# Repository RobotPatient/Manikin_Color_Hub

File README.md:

# Manikin_Color_Hub

Welcome to the Manikin Color Hub, a part of the skin color research team RGBbaby. 
Here's an overview of our file structure:

# Manikin Colour Hub

## Led Driver Board Files, Flexible LED Strip PCBs, and Software

Welcome to the Manikin Colour Hub, a part of the skin colour research group RGBbaby. Here's an overview of our file structure:

### Arduino Spectrometer:

Contains CAD and code files for the AS7341 colour sensor. Use this sensor setup to analyze the light emitted by a specific sample.

### General Docs:

- **Product_report - individual reports:** Individual project files included in the product report.
- **Product Report:** Detailed report on our project.
- **Progress Report:** Overview of our progress.
- **Initial Questions and Answers from WKZ:** Compilation of our initial queries and responses.
- **Manual:** Comprehensive guide for our project.
- **ToDo List:** List of tasks yet to be completed.

### Led Test Setup:

Code for testing a bare neopixel LED strip in combination with an Adafruit Feather M0 Express.

### PCBs:

- **LedDriverBoardV1:** KiCad files and schematic for the first version of our LED driver board.
- **LedDriverBoardV2:** KiCad files, schematic, code, and flexible PCBs for the second version of our LED driver board.
- **LedDriverBoardV3:** KiCad files, schematic, code, and flexible PCBs for the third and final version of our LED driver board.

### Pi Spectrometer:

CAD files for the Raspberry Pi-based spectrometer.

Feel free to explore and contribute to the Manikin Color Hub's diverse set of files and resources. 
If you have questions, reach out to us!

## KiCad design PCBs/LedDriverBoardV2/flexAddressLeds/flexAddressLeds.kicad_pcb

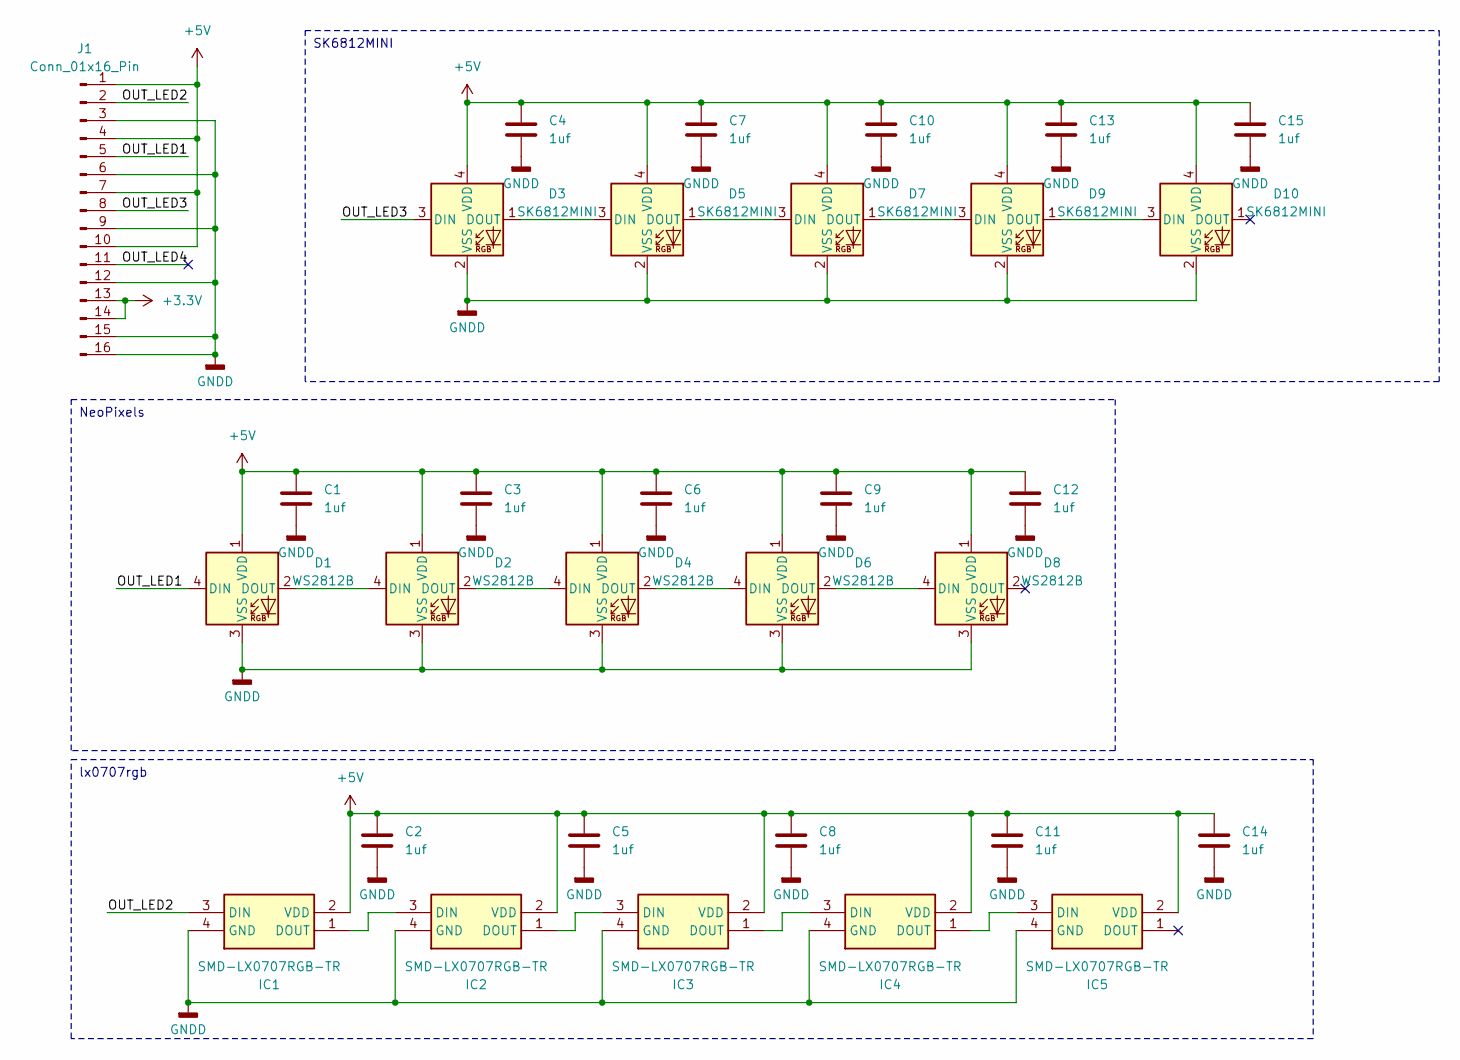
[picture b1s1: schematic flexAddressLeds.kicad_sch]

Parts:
C1, C2, C3, C4, C5, C6, C7, C8, C9, C10, C11, C12, C13, C14, C15: 1uf; C_0603_1608Metric_Pad1.08x0.95mm_HandSolder
D1, D2, D4, D6, D8: WS2812B; LED_WS2812B_PLCC4_5.0x5.0mm_P3.2mm
D3, D5, D7, D9, D10: SK6812MINI; LED_SK6812MINI_PLCC4_3.5x3.5mm_P1.75mm
IC1, IC2, IC3, IC4, IC5: SMD-LX0707RGB-TR; SMDLX0707RGBTR; Manufacturer_Part_Number SMD-LX0707RGB-TR; Mouser Part Number 696-SMDLX0707RGBTR
J1: Conn_01x16_Pin; Conn_1x16_FFC

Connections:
+3.3V: J1.13, J1.14
+5V: C1.1, C2.1, C3.1, C4.1, C5.1, C6.1, C7.1, C8.1, C9.1, C10.1, C11.1, C12.1, C13.1, C14.1, C15.1, D1.1 (VDD), D2.1 (VDD), D3.4 (VDD), D4.1 (VDD), D5.4 (VDD), D6.1 (VDD), D7.4 (VDD), D8.1 (VDD), D9.4 (VDD), D10.4 (VDD), IC1.2 (VDD), IC2.2 (VDD), IC3.2 (VDD), IC4.2 (VDD), IC5.2 (VDD), J1.1, J1.4, J1.7, J1.10
/OUT_LED1: D1.4 (DIN), J1.5
/OUT_LED2: IC1.3 (DIN), J1.2
/OUT_LED3: D3.3 (DIN), J1.8
/OUT_LED4: J1.11
GNDD: C1.2, C2.2, C3.2, C4.2, C5.2, C6.2, C7.2, C8.2, C9.2, C10.2, C11.2, C12.2, C13.2, C14.2, C15.2, D1.3 (VSS), D2.3 (VSS), D3.2 (VSS), D4.3 (VSS), D5.2 (VSS), D6.3 (VSS), D7.2 (VSS), D8.3 (VSS), D9.2 (VSS), D10.2 (VSS), IC1.4 (GND), IC2.4 (GND), IC3.4 (GND), IC4.4 (GND), IC5.4 (GND), J1.3, J1.6, J1.9, J1.12, J1.15, J1.16
unnamed: D1.2 (DOUT), D2.4 (DIN)
unnamed: D2.2 (DOUT), D4.4 (DIN)
unnamed: D3.1 (DOUT), D5.3 (DIN)
unnamed: D4.2 (DOUT), D6.4 (DIN)
unnamed: D5.1 (DOUT), D7.3 (DIN)
unnamed: D6.2 (DOUT), D8.4 (DIN)
unnamed: D7.1 (DOUT), D9.3 (DIN)
unnamed: D9.1 (DOUT), D10.3 (DIN)
unnamed: IC1.1 (DOUT), IC2.3 (DIN)
unnamed: IC2.1 (DOUT), IC3.3 (DIN)
unnamed: IC3.1 (DOUT), IC4.3 (DIN)
unnamed: IC4.1 (DOUT), IC5.3 (DIN)

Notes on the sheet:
lx0707rgb
NeoPixels
SK6812MINI

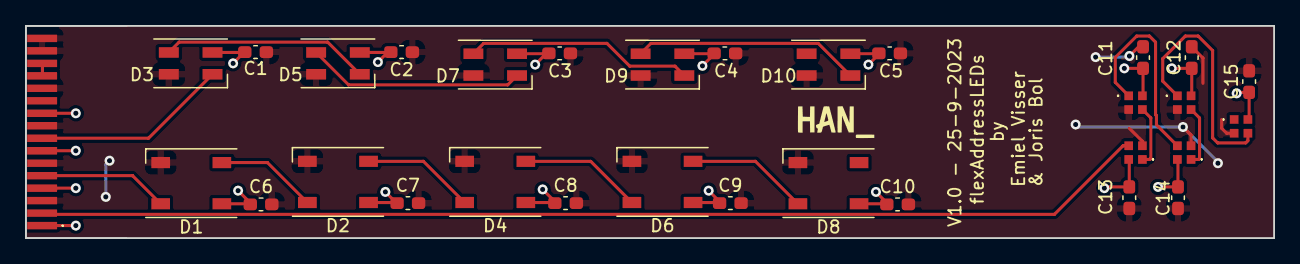
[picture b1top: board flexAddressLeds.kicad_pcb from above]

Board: 2 copper layers, 100.0 x 17.0 mm, 31 parts (0 on the bottom side), 18 nets.

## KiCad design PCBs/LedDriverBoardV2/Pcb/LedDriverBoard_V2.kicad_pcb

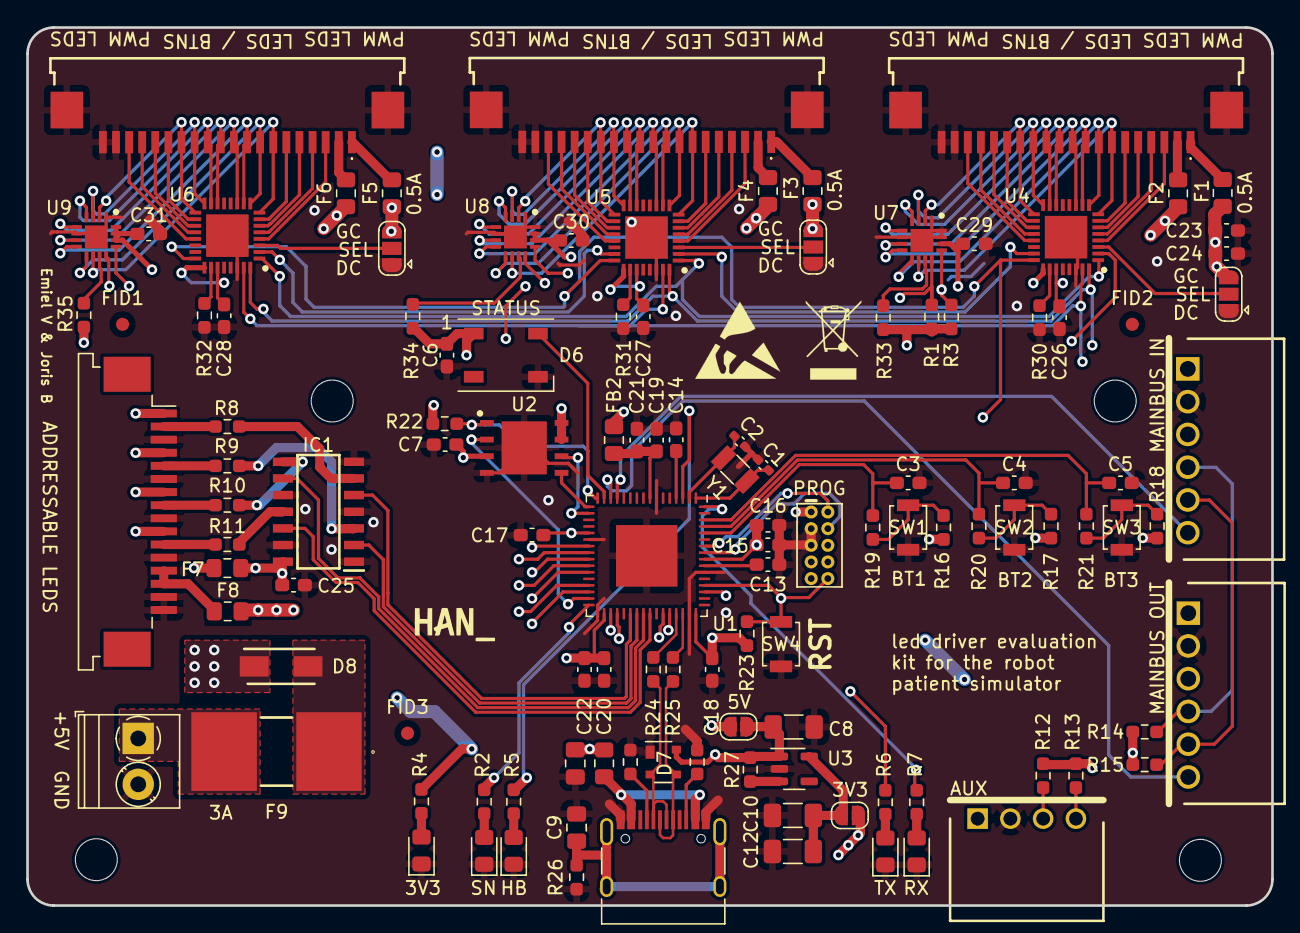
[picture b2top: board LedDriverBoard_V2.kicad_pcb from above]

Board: 4 copper layers, 95.0 x 67.0 mm, 122 parts (0 on the bottom side), 136 nets.

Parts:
C1, C2: 2pF; C_0402_1005Metric_Pad0.74x0.62mm_HandSolder
C3, C4, C5, C13, C16, C21, C22: 10uF; C_0603_1608Metric_Pad1.08x0.95mm_HandSolder
C6, C14: 1uF; C_0603_1608Metric_Pad1.08x0.95mm_HandSolder
C7, C15, C17, C18, C19, C20, C23, C25, C26, C27, C28, C29, C30, C31: 100nF; C_0603_1608Metric_Pad1.08x0.95mm_HandSolder
C8, C10: 10uF; C_1206_3216Metric_Pad1.33x1.80mm_HandSolder
C9: 4.7nF 1kV; C_0805_2012Metric_Pad1.18x1.45mm_HandSolder
C11: 100uF; C_0805_2012Metric_Pad1.18x1.45mm_HandSolder
C12: 1uF; C_1206_3216Metric_Pad1.33x1.80mm_HandSolder
C24: 4.7uF; C_0603_1608Metric_Pad1.08x0.95mm_HandSolder
D1: BLUE; LED_0805_2012Metric_Pad1.15x1.40mm_HandSolder
D2, D4: GREEN; LED_0805_2012Metric_Pad1.15x1.40mm_HandSolder
D3: RED; LED_0805_2012Metric_Pad1.15x1.40mm_HandSolder
D5: ORANGE; LED_0805_2012Metric_Pad1.15x1.40mm_HandSolder
D6: WS2812B; LED_WS2812B_PLCC4_5.0x5.0mm_P3.2mm
D7: PRTR5V0U2X; SOT-143
D8: D_Schottky; DIOM5127X229N
F1, F2, F3, F4, F5, F6, F7, F8: Polyfuse; Fuse_0805_2012Metric_Pad1.15x1.40mm_HandSolder
F9: Fuse; 0031.7701.11
FB1, FB2: FerriteBead; L_0805_2012Metric_Pad1.15x1.40mm_HandSolder
FID1, FID2, FID3: Fiducial; Fiducial_1mm_Mask2mm
H1, H2, H3, H4: MountingHole; MountingHole_3.2mm_M3_DIN965
IC1: SN74AHCT125DR; SOIC127P600X175-14N
J1, J2, J3: FFC3B11-20-T; FFC3B1120T
J4: 1778641; SHDRRA4W60P0X250_1X4_1170X750X510P
J5: Conn_01x16_Pin; TE_1-84952-6_1x16-1MP_P1.0mm_Horizontal
J6, J7: 1778667; SHDRRA6W70P0X250_1X6_1670X750X510P
J8: CORTEX_DEBUGPTH; 2X5-PTH-1.27MM
J9: USB_C_Receptacle_USB2.0; USB_C_Receptacle_HRO_TYPE-C-31-M-12
J10: Conn_01x02_Socket; TerminalBlock_Phoenix_PT-1,5-2-3.5-H_1x02_P3.50mm_Horizontal
JP1, JP2: Jumper_2_Open; SolderJumper-2_P1.3mm_Open_RoundedPad1.0x1.5mm
JP3, JP4, JP5: Jumper_3_Open; SolderJumper-3_P1.3mm_Open_RoundedPad1.0x1.5mm
R1, R3, R12, R13, R14, R15: 4.7k; R_0603_1608Metric_Pad0.98x0.95mm_HandSolder
R2, R5, R7: 330; R_0603_1608Metric_Pad0.98x0.95mm_HandSolder
R4, R6: 470; R_0603_1608Metric_Pad0.98x0.95mm_HandSolder
R8, R9, R10, R11: 62; R_0603_1608Metric_Pad0.98x0.95mm_HandSolder
R16, R17, R18, R19, R20, R21, R22, R23, R33, R34, R35: 10k; R_0603_1608Metric_Pad0.98x0.95mm_HandSolder
R24, R25: 27; R_0603_1608Metric_Pad0.98x0.95mm_HandSolder
R26: 1m; R_0603_1608Metric_Pad0.98x0.95mm_HandSolder
R27: 100k; R_0603_1608Metric_Pad0.98x0.95mm_HandSolder
R28, R29: 5.1k 1%; R_0603_1608Metric_Pad0.98x0.95mm_HandSolder
R30, R31, R32: 2k; R_0603_1608Metric_Pad0.98x0.95mm_HandSolder
SW1, SW2, SW3, SW4: SW_Push; SW_SPST_B3U-1000P
U1: ATSAMD21J18A-M; QFN-64-1EP_9x9mm_P0.5mm_EP4.7x4.7mm
U2: IS25LP032D-JLLE; SON127P600X500X75-9N-D
U3: AP2112K-3.3; SOT-23-5
U4, U5, U6: TLC59401RHBR; QFN50P500X500X100-33N-D
U7, U8, U9: PCA9670BS,118; QFN50P300X300X100-17N-D
Y1: 32.768mHz; Crystal_SMD_3215-2Pin_3.2x1.5mm

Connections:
+3V3: C6.2, C7.2, C15.1, C16.1, C17.1, C18.1, C20.1, C22.1, C29.1, C30.1, C31.1, D6.1 (VDD), F2.1, F4.1, F6.1, F8.2, FB2.1, J4.1, J6.3, J7.3, J8.1 (VCC), JP2.2 (B), R1.1, R3.2, R4.1, R12.1, R13.2, R14.1, R15.2, R16.1, R17.1, R18.1, R22.1, R23.2, R33.2, R34.2, R35.2, U1.21 (VDDIO), U1.34 (VDDIO), U1.48 (VDDIO), U1.56 (VDDIN), U2.3 (~WP(IO2)), U2.7 (~HOLD(IO3)), U2.8 (VCC), U7.14 (VDD), U8.14 (VDD), U8.15 (AD0), U9.14 (VDD), U9.15 (AD0), U9.16 (AD1)
+5V: C23.1, C24.1, C25.1, C26.1, C27.1, C28.1, D8.1 (K), F1.1, F3.1, F5.1, F7.2, IC1.14 (VCC), J6.1, J7.1, JP1.2 (B), JP3.3 (B), JP4.3 (B), JP5.3 (B), U4.25 (TEST), U4.27 (VCC), U5.25 (TEST), U5.27 (VCC), U6.25 (TEST), U6.27 (VCC)
/ADR_LED1: IC1.2 (1A), U1.39 (PB16)
/ADR_LED2: IC1.5 (2A), U1.38 (PA19)
/ADR_LED3: IC1.9 (3A), U1.40 (PB17)
/ADR_LED4: IC1.12 (4A), U1.41 (PA20)
/AREF: C14.1, U1.4 (PA03)
/BTN1: C3.1, R19.2, U1.60 (PB31)
/BTN2: C4.1, R20.2, U1.61 (PB00)
/BTN3: C5.1, R21.2, U1.62 (PB01)
/D2_FLASHMISO: U1.31 (PA14), U2.2 (SO(IO1))
/D3_FLASHSCK: U1.18 (PA09), U2.6 (SCK)
/D4_FLASHMOSI: U1.17 (PA08), U2.5 (SI(IO0))
/D5_HEALTH: R2.1, U1.32 (PA15)
/D8_NEOPIXEL: D6.4 (DIN), U1.15 (PA06)
/D14_HB: R5.1, U1.3 (PA02)
/INT4: J6.6, U1.13 (PA04)
/INT5: J7.6, U1.14 (PA05)
/LED1-0: J1.3, U4.4 (OUT0)
/LED1-1: J1.4, U4.5 (OUT1)
/LED1-2: J1.5, U4.6 (OUT2)
/LED1-3: J1.6, U4.7 (OUT3)
/LED1-4: J1.7, U4.8 (OUT4), U7.10 (P7)
/LED1-5: J1.8, U4.9 (OUT5), U7.9 (P6)
/LED1-6: J1.9, U4.10 (OUT6), U7.8 (P5)
/LED1-7: J1.10, U4.11 (OUT7), U7.7 (P4)
/LED1-8: J1.11, U4.14 (OUT8), U7.5 (P3)
/LED1-9: J1.12, U4.15 (OUT9), U7.4 (P2)
/LED1-10: J1.13, U4.16 (OUT10), U7.3 (P1)
/LED1-11: J1.14, U4.17 (OUT11), U7.2 (P0)
/LED1-12: J1.15, U4.18 (OUT12)
/LED1-13: J1.16, U4.19 (OUT13)
/LED1-14: J1.17, U4.20 (OUT14)
/LED1-15: J1.18, U4.21 (OUT15)
/LED2-0: J2.3, U5.4 (OUT0)
/LED2-1: J2.4, U5.5 (OUT1)
/LED2-2: J2.5, U5.6 (OUT2)
/LED2-3: J2.6, U5.7 (OUT3)
/LED2-4: J2.7, U5.8 (OUT4), U8.10 (P7)
/LED2-5: J2.8, U5.9 (OUT5), U8.9 (P6)
/LED2-6: J2.9, U5.10 (OUT6), U8.8 (P5)
/LED2-7: J2.10, U5.11 (OUT7), U8.7 (P4)
/LED2-8: J2.11, U5.14 (OUT8), U8.5 (P3)
/LED2-9: J2.12, U5.15 (OUT9), U8.4 (P2)
/LED2-10: J2.13, U5.16 (OUT10), U8.3 (P1)
/LED2-11: J2.14, U5.17 (OUT11), U8.2 (P0)
/LED2-12: J2.15, U5.18 (OUT12)
/LED2-13: J2.16, U5.19 (OUT13)
/LED2-14: J2.17, U5.20 (OUT14)
/LED2-15: J2.18, U5.21 (OUT15)
/LED3-0: J3.3, U6.4 (OUT0)
/LED3-1: J3.4, U6.5 (OUT1)
/LED3-2: J3.5, U6.6 (OUT2)
/LED3-3: J3.6, U6.7 (OUT3)
/LED3-4: J3.7, U6.8 (OUT4), U9.10 (P7)
/LED3-5: J3.8, U6.9 (OUT5), U9.9 (P6)
/LED3-6: J3.9, U6.10 (OUT6), U9.8 (P5)
/LED3-7: J3.10, U6.11 (OUT7), U9.7 (P4)
/LED3-8: J3.11, U6.14 (OUT8), U9.5 (P3)
/LED3-9: J3.12, U6.15 (OUT9), U9.4 (P2)
/LED3-10: J3.13, U6.16 (OUT10), U9.3 (P1)
/LED3-11: J3.14, U6.17 (OUT11), U9.2 (P0)
/LED3-12: J3.15, U6.18 (OUT12)
/LED3-13: J3.16, U6.19 (OUT13)
/LED3-14: J3.17, U6.20 (OUT14)
/LED3-15: J3.18, U6.21 (OUT15)
/LEDBLANK: U1.27 (PB14), U4.31 (BLANK), U5.31 (BLANK), U6.31 (BLANK)
/LEDGSLCK: U1.26 (PB13), U4.24 (GSCLK), U5.24 (GSCLK), U6.24 (GSCLK)
/LEDSCLK: U1.24 (PB11), U4.1 (SCLK), U5.1 (SCLK), U6.1 (SCLK)
/LEDSIN: U1.23 (PB10), U4.2 (SIN)
/LEDXLAT: U1.25 (PB12), U4.32 (XLAT), U5.32 (XLAT), U6.32 (XLAT)
/LedDriver/LEDMODE1: JP3.2 (C), U4.3 (MODE)
/LedDriver/LEDMODE2: JP5.2 (C), U5.3 (MODE)
/LedDriver/LEDMODE3: JP4.2 (C), U6.3 (MODE)
/LedDriver/LEDSOUT-1: U4.23 (SOUT), U5.2 (SIN)
/LedDriver/LEDSOUT-2: U5.23 (SOUT), U6.2 (SIN)
/OUT_LED1: IC1.3 (1Y), R9.1
/OUT_LED2: IC1.6 (2Y), R8.1
/OUT_LED3: IC1.8 (3Y), R10.1
/OUT_LED4: IC1.11 (4Y), R11.1
/PA0_XTAL: C1.2, U1.1 (PA00), Y1.2
/PA1_XTAL: C2.2, U1.2 (PA01), Y1.1
/PA7_FLASH_CS: R22.2, U1.16 (PA07), U2.1 (~CE)
/Power/3.3v: C10.1, C12.1, JP2.1 (A), U3.5 (VOUT)
/Power/SHIELD: C9.1, J9.S1 (SHIELD), R26.1
/RXLED: R7.1, U1.64 (PB03)
/SCL: J6.4, J7.4, R14.2, U1.44 (PA23)
/SCL_IO: R1.2, U1.36 (PA17), U7.12 (SCL), U8.12 (SCL), U9.12 (SCL)
/SCL_SENSOR_D13: J4.3, R12.2, U1.30 (PA13)
/SDA: J6.5, J7.5, R15.1, U1.43 (PA22)
/SDA_IO: R3.1, U1.35 (PA16), U7.13 (SDA), U8.13 (SDA), U9.13 (SDA)
/SDA_SENSOR_D11: J4.4, R13.1, U1.29 (PA12)
/SWCLK: J8.4 (SWDCLK/TCK), U1.57 (PA30)
/SWDIO: J8.2 (SWDIO/TMS), U1.58 (PA31)
/TXLED: R6.1, U1.51 (PA27)
/USB_D+: D7.3 (I/O2), J9.A6 (D+), J9.B6 (D+), R25.1
/USB_D-: D7.2 (I/O1), J9.A7 (D-), J9.B7 (D-), R24.1
/USB_TERM_D+: R25.2, U1.46 (PA25)
/USB_TERM_D-: R24.2, U1.45 (PA24)
/VDDANA: C19.1, C21.1, FB2.2, U1.8 (VDDANA)
/VDDCORE: C13.2, U1.55 (VDDCORE)
/~RESET: J8.10 (NRESET), R23.1, SW4.1, U1.52 (~RESET)
GNDD: C1.1, C2.1, C3.2, C4.2, C5.2, C6.1, C7.1, C8.2, C9.2, C10.2, C11.2, C12.2, C13.1, C14.2, C15.2, C16.2, C17.2, C18.2, C19.2, C20.2, C21.2, C22.2, C23.2, C24.2, C25.2, C26.2, C27.2, C28.2, C29.2, C30.2, C31.2, D1.1 (K), D2.1 (K), D3.1 (K), D4.1 (K), D5.1 (K), D6.3 (VSS), D7.1 (GND), IC1.1 (1~OE), IC1.4 (2~OE), IC1.7 (GND), IC1.10 (3~OE), IC1.13 (4~OE), J1.19, J1.20, J1.MP1, J1.MP2, J2.19, J2.20, J2.MP1, J2.MP2, J3.19, J3.20, J3.MP1, J3.MP2, J4.2, J5.3, J5.6, J5.9, J5.12, J5.15, J5.16, J6.2, J7.2, J8.3 (GND), J8.5 (GND), J9.A1 (GND), J9.A12 (GND), J9.B1 (GND), J9.B12 (GND), J10.2, JP3.1 (A), JP4.1 (A), JP5.1 (A), R26.2, R28.2, R29.2, R30.2, R31.2, R32.2, SW1.1, SW2.1, SW3.1, SW4.2, U1.7 (GNDANA), U1.22 (GND), U1.33 (GND), U1.47 (GND), U1.54 (GND), U1.65 (EP), U2.4 (GND), U2.9 (EP), U3.2 (GND), U4.30 (GND), U4.33 (EP), U5.30 (GND), U5.33 (EP), U6.30 (GND), U6.33 (EP), U7.1 (AD2), U7.6 (VSS), U7.15 (AD0), U7.16 (AD1), U7.17 (EP), U8.1 (AD2), U8.6 (VSS), U8.16 (AD1), U8.17 (EP), U9.1 (AD2), U9.6 (VSS), U9.17 (EP)
unnamed: D1.2 (A), R2.2
unnamed: D2.2 (A), R4.2
unnamed: D3.2 (A), R5.2
unnamed: D4.2 (A), R6.2
unnamed: D5.2 (A), R7.2
unnamed: D8.2 (A), F9.1
unnamed: F1.2, J1.1
unnamed: F2.2, J1.2
unnamed: F3.2, J2.1
unnamed: F4.2, J2.2
unnamed: F5.2, J3.1
unnamed: F6.2, J3.2
unnamed: FB1.1, J9.A4 (VBUS), J9.A9 (VBUS), J9.B4 (VBUS), J9.B9 (VBUS)
unnamed: F7.1, J5.1, J5.4, J5.7, J5.10
unnamed: J5.2, R8.2
unnamed: J5.5, R9.2
unnamed: J5.8, R10.2
unnamed: J5.11, R11.2
unnamed: F8.1, J5.13, J5.14
unnamed: J9.A5 (CC1), R29.1
unnamed: J9.B5 (CC2), R28.1
unnamed: F9.2, J10.1
unnamed: R16.2, R19.1, SW1.2
unnamed: R17.2, R20.1, SW2.2
unnamed: R18.2, R21.1, SW3.2
unnamed: R27.2, U3.3 (EN)
unnamed: R30.1, U4.26 (IREF)
unnamed: R31.1, U5.26 (IREF)
unnamed: R32.1, U6.26 (IREF)
unnamed: R33.1, U7.11 (~RESET)
unnamed: R34.1, U8.11 (~RESET)
unnamed: R35.1, U9.11 (~RESET)
VBUS: C8.1, C11.1, D7.4 (VCC), FB1.2, JP1.1 (A), R27.1, U3.1 (VIN)

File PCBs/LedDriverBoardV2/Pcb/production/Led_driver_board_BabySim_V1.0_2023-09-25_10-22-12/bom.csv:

Designator,Footprint,Quantity,Value,LCSC Part #
"C1, C2",0402,2,2pF,
"C10, C8",1206,2,10uF,
C11,0805,1,100uF,
C12,1206,1,1uF,
"C13, C16, C21, C22, C3, C4, C5",0603,7,10uF,
"C14, C6",0603,2,1uF,
"C15, C17, C18, C19, C20, C23, C25, C26, C27, C28, C29, C30, C31, C7",0603,14,100nF,
C24,0603,1,4.7uF,
C9,0805,1,4.7nF 1kV,
D1,0805,1,BLUE,
"D2, D4",0805,2,GREEN,
D3,0805,1,RED,
D5,0805,1,ORANGE,
D6,LED_WS2812B_PLCC4_5.0x5.0mm_P3.2mm,1,WS2812B,
D7,SOT-143,1,PRTR5V0U2X,
D8,DIOM5127X229N,1,D_Schottky,
"F1, F2, F3, F4, F5, F6, F7, F8",0805,8,Polyfuse,
F9,0031.7701.11,1,Fuse,
"FB1, FB2",0805,2,FerriteBead,
"FID1, FID2, FID3",Fiducial_1mm_Mask2mm,3,Fiducial,
"H1, H2, H3, H4",MountingHole_3.2mm_M3_DIN965,4,MountingHole,
IC1,SOIC127P600X175-14N,1,SN74AHCT125DR,
"J1, J2, J3",FFC3B1120T,3,FFC3B11-20-T,
J10,"TerminalBlock_Phoenix_PT-1,5-2-3.5-H_1x02_P3.50mm_Horizontal",1,Conn_01x02_Socket,
J4,SHDRRA4W60P0X250_1X4_1170X750X510P,1,1778641,
J5,TE_1-84952-6_1x16-1MP_P1.0mm_Horizontal,1,Conn_01x16_Pin,
"J6, J7",SHDRRA6W70P0X250_1X6_1670X750X510P,2,1778667,
J8,2X5-PTH-1.27MM,1,CORTEX_DEBUGPTH,
J9,USB_C_Receptacle_HRO_TYPE-C-31-M-12,1,USB_C_Receptacle_USB2.0,
"JP1, JP2",SolderJumper-2_P1.3mm_Open_RoundedPad1.0x1.5mm,2,Jumper_2_Open,
"JP3, JP4, JP5",SolderJumper-3_P1.3mm_Open_RoundedPad1.0x1.5mm,3,Jumper_3_Open,
"R1, R12, R13, R14, R15, R3",0603,6,4.7k,
"R10, R11, R8, R9",0603,4,62,
"R16, R17, R18, R19, R20, R21, R22, R23, R33, R34, R35",0603,11,10k,
"R2, R5, R7",0603,3,330,
"R24, R25",0603,2,27,
R26,0603,1,1m,
R27,0603,1,100k,
"R28, R29",0603,2,5.1k 1%,
"R30, R31, R32",0603,3,2k,
"R4, R6",0603,2,470,
"SW1, SW2, SW3, SW4",SW_SPST_B3U-1000P,4,SW_Push,
U1,QFN-64-1EP_9x9mm_P0.5mm_EP4.7x4.7mm,1,ATSAMD21J18A-M,
U2,SON127P600X500X75-9N-D,1,IS25LP032D-JLLE,
U3,SOT-23-5,1,AP2112K-3.3,
"U4, U5, U6",QFN50P500X500X100-33N-D,3,TLC59401RHBR,
"U7, U8, U9",QFN50P300X300X100-17N-D,3,"PCA9670BS,118",
Y1,Crystal_SMD_3215-2Pin_3.2x1.5mm,1,32.768mHz,

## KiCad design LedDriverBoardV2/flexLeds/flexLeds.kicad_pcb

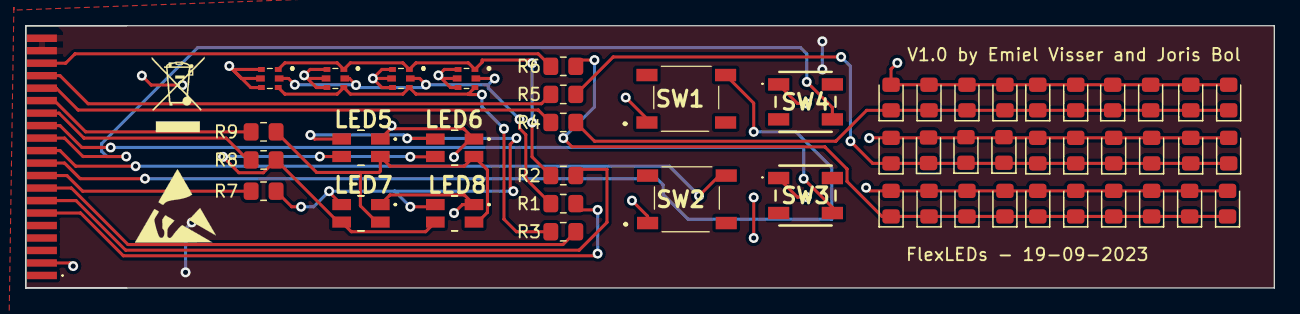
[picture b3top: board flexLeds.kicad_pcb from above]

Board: 2 copper layers, 100.0 x 21.0 mm, 52 parts (0 on the bottom side), 24 nets.

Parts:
D1, D2, D3, D4, D5, D6, D7, D8, D9, D10: RED; LED_0805_2012Metric_Pad1.15x1.40mm_HandSolder
D11, D12, D13, D14, D15, D16, D17, D18, D19, D20: GREEN; LED_0805_2012Metric_Pad1.15x1.40mm_HandSolder
D21, D22, D23, D24, D25, D26, D27, D28, D29, D30: BLUE; LED_0805_2012Metric_Pad1.15x1.40mm_HandSolder
J1: Conn_01x20_Pin; Conn_1x20_FFC
LED1, LED2, LED3, LED4: 19-337C_RSBHGHC-A01_2T; 19337CRSBHGHCA012T
LED5, LED6, LED7, LED8: 150141M173100
R1, R2, R3, R4, R5, R6, R7, R8, R9: R; R_0805_2012Metric_Pad1.20x1.40mm_HandSolder
SW1, SW2: SW_Push_Dual; TL3342F260QG
SW3, SW4: SW_Push_Dual; TS174805YE160SMTTR

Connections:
+3V3: D1.2 (A), D2.2 (A), D3.2 (A), D4.2 (A), D5.2 (A), D6.2 (A), D7.2 (A), D8.2 (A), D9.2 (A), D10.2 (A), D11.2 (A), D12.2 (A), D13.2 (A), D14.2 (A), D15.2 (A), D16.2 (A), D17.2 (A), D18.2 (A), D19.2 (A), D20.2 (A), D21.2 (A), D22.2 (A), D23.2 (A), D24.2 (A), D25.2 (A), D26.2 (A), D27.2 (A), D28.2 (A), D29.2 (A), D30.2 (A), J1.2, LED1.2 (A_GREEN), LED1.4 (A_RED), LED1.6 (A_BLUE), LED2.2 (A_GREEN), LED2.4 (A_RED), LED2.6 (A_BLUE), LED3.2 (A_GREEN), LED3.4 (A_RED), LED3.6 (A_BLUE), LED4.2 (A_GREEN), LED4.4 (A_RED), LED4.6 (A_BLUE), LED5.1 (COM_A), LED6.1 (COM_A), LED7.1 (COM_A), LED8.1 (COM_A), SW1.1, SW2.1, SW3.1, SW4.1
/LED-3: J1.6, R1.1
/LED-4: J1.7, R2.1
/LED-5: J1.8, R3.1
/LED-6: J1.9, R7.1
/LED-7: J1.10, SW1.4
/LED-8: J1.11, SW2.4
/LED-9: J1.12, SW4.4
/LED-10: J1.13, SW3.4
/LED-11: J1.14, R8.1
/LED-12: J1.15, R9.1
/LED-13: J1.16, R4.2
/LED-14: J1.17, R5.2
/LED-15: J1.18, R6.2
GNDD: J1.19, J1.20
unnamed: D1.1 (K), D2.1 (K), D3.1 (K), D4.1 (K), D5.1 (K), D6.1 (K), D7.1 (K), D8.1 (K), D9.1 (K), D10.1 (K), R4.1
unnamed: D11.1 (K), D12.1 (K), D13.1 (K), D14.1 (K), D15.1 (K), D16.1 (K), D17.1 (K), D18.1 (K), D19.1 (K), D20.1 (K), R5.1
unnamed: D21.1 (K), D22.1 (K), D23.1 (K), D24.1 (K), D25.1 (K), D26.1 (K), D27.1 (K), D28.1 (K), D29.1 (K), D30.1 (K), R6.1
unnamed: LED1.5 (K_BLUE), LED2.5 (K_BLUE), LED3.5 (K_BLUE), LED4.5 (K_BLUE), R3.2
unnamed: LED1.1 (K_GREEN), LED2.1 (K_GREEN), LED3.1 (K_GREEN), LED4.1 (K_GREEN), R2.2
unnamed: LED1.3 (K_RED), LED2.3 (K_RED), LED3.3 (K_RED), LED4.3 (K_RED), R1.2
unnamed: LED5.2 (K_B), LED6.2 (K_B), LED7.2 (K_B), LED8.2 (K_B), R9.2
unnamed: LED5.4 (K_G), LED6.4 (K_G), LED7.4 (K_G), LED8.4 (K_G), R8.2
unnamed: LED5.3 (K_R), LED6.3 (K_R), LED7.3 (K_R), LED8.3 (K_R), R7.2

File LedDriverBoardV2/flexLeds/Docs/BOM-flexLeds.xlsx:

Catagory | Name in schematic: | Name/Value | Mounting type | Footprint: | Nr. per. PCB: | Amount of PCBs: | Total amount: | To order: | Price per.part: | Price total: | Link:
LED | D6,D4,D5,D3,D9,D7,D1,D8,D10,D2 | RED | SMD | 0805 | 10 | 2 | 20 | 30 | 0.251 | 7.53 | https://nl.mouser.com/ProductDetail/Lite-On/LTST-C171KRKT?qs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
LED | D11,D19,D18,D14,D16,D13,D17,D15,D20,D12 | GREEN | SMD | 0805 | 10 | 2 | 20 | 30 | 0.214 | 6.42 | https://nl.mouser.com/ProductDetail/Lite-On/LTST-C171GKT?qs=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
LED | D30,D24,D21,D28,D22,D26,D27,D25,D29,D23 | BLUE | SMD | 0805 | 10 | 2 | 20 | 30 | 0.28799999999999998 | 8.6399999999999988 | https://nl.mouser.com/ProductDetail/Lite-On/LTST-C171TBKT?qs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
LED | LED8,LED7,LED5,LED6 | 150141M173100 | SMD | 150141M173100 | 4 | 2 | 8 | 10 | 0.46 | 4.6000000000000005 | https://nl.mouser.com/ProductDetail/Wurth-Elektronik/150141M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
LED | LED3,LED4,LED2,LED1 | 19337CRSBHGHCA012T | SMD | 19337CRSBHGHCA012T | 4 | 2 | 8 | 10 | 0.3 | 3 | https://www.digikey.nl/en/products/detail/everlight-electron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
SWITCH | SW2,SW1 | TL3342F260QG | SMD | TL3342F260QG | 2 | 2 | 4 | 5 | 0.61 | 3.05 | https://nl.mouser.com/ProductDetail/E-Switch/TL3342F260QG?qs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
SWITCH | SW3,SW4 | TS174805YE160SMTTR | SMD | TS174805YE160SMTTR | 2 | 2 | 4 | 5 | 0.26 | 1.3 | https://nl.mouser.com/ProductDetail/CUI-Devices/TS17-48-05-Y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
RESISTOR | R4, R5, R6 | 20ohm | SMD | 0805 | 3 | 2 | 6 | 10 | 4.7E-2 | 0.47 | https://nl.mouser.com/ProductDetail/Panasonic/ERJ-P06J200V?q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
RESISTOR | R1, R2, R3, R7, R8, R9 | 165ohm | SMD | 0805 | 6 | 2 | 12 | 20 | 0.16 | 3.2 | https://nl.mouser.com/ProductDetail/Panasonic/ERJ-P06F1650V?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
 |  |  |  |  |  |  | Amount of PCBs | #REF! | Total: | 38.209999999999994

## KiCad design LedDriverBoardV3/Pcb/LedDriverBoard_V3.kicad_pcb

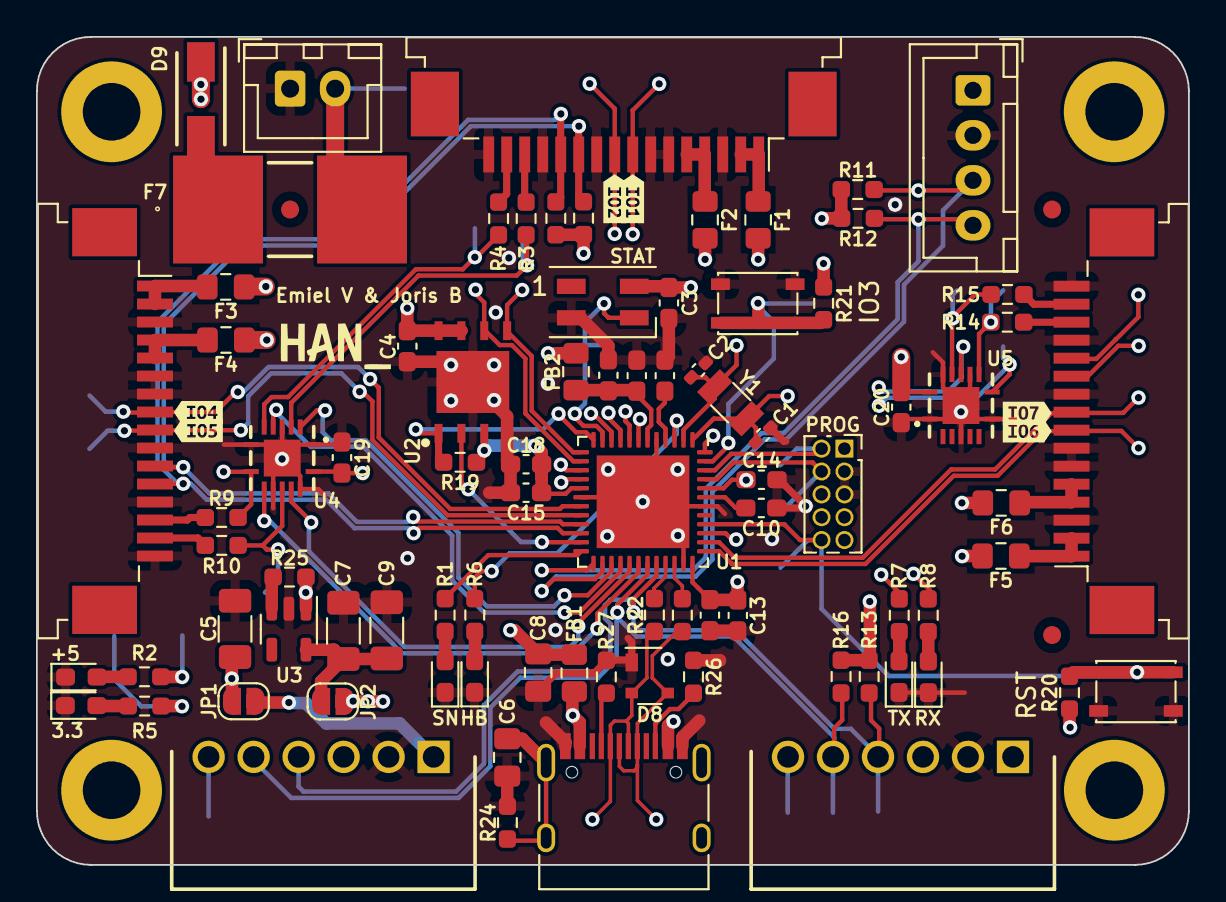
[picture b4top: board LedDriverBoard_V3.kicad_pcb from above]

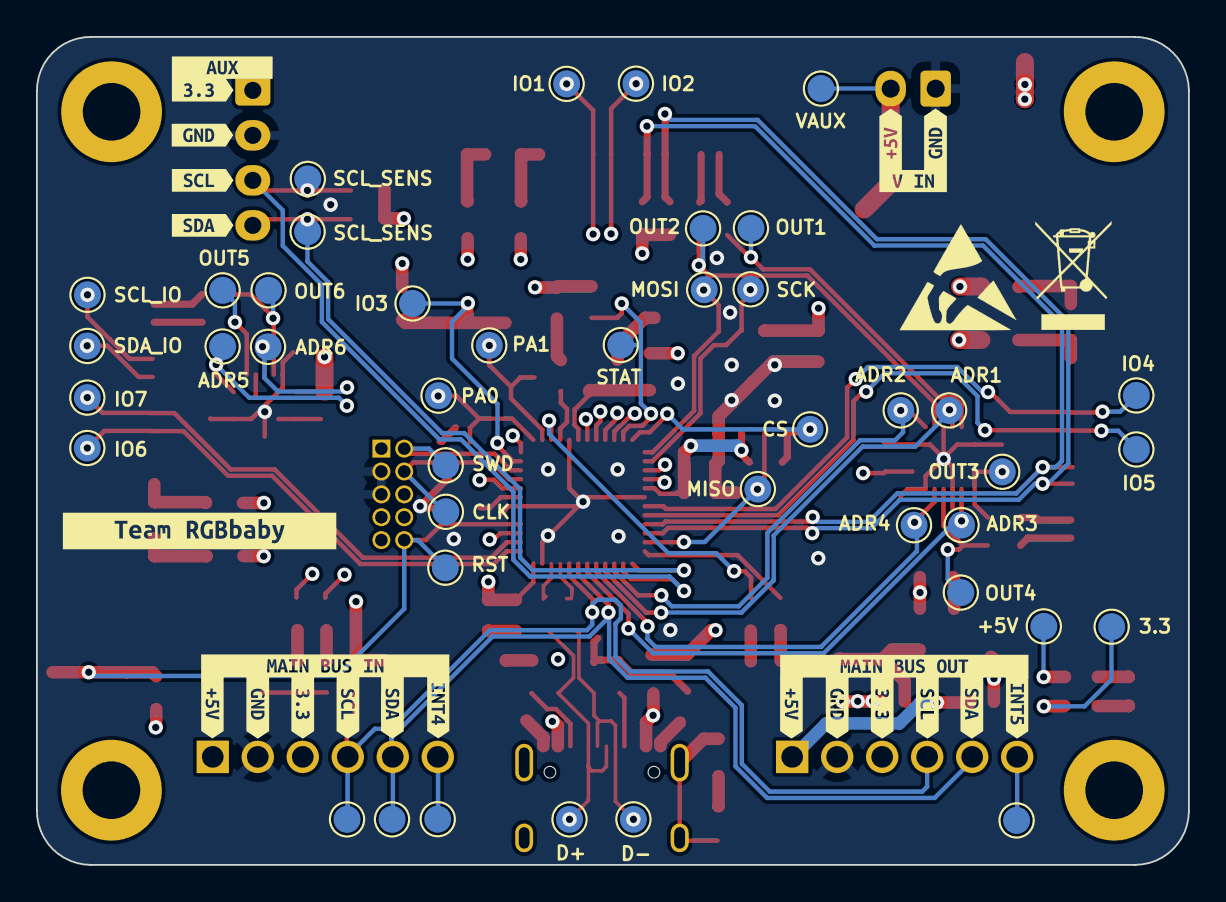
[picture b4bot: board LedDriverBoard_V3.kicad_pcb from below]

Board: 4 copper layers, 64.0 x 46.0 mm, 162 parts (65 on the bottom side), 78 nets.

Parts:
C1, C2: 15pF; C_0402_1005Metric_Pad0.74x0.62mm_HandSolder
C3, C11: 1uF; C_0603_1608Metric_Pad1.08x0.95mm_HandSolder
C4, C12, C14, C15, C16, C19, C20: 100nF; C_0603_1608Metric_Pad1.08x0.95mm_HandSolder
C5, C7: 10uF; C_1206_3216Metric_Pad1.33x1.80mm_HandSolder
C6: 4.7nF 1kV; C_0805_2012Metric_Pad1.18x1.45mm_HandSolder
C8: 100uF; C_0805_2012Metric_Pad1.18x1.45mm_HandSolder
C9: 1uF; C_1206_3216Metric_Pad1.33x1.80mm_HandSolder
C10, C13, C17, C18: 10uF; C_0603_1608Metric_Pad1.08x0.95mm_HandSolder
D1: BLUE; LED_0603_1608Metric_Pad1.05x0.95mm_HandSolder
D2, D4: RED; LED_0603_1608Metric_Pad1.05x0.95mm_HandSolder
D3, D5: GREEN; LED_0603_1608Metric_Pad1.05x0.95mm_HandSolder
D6: ORANGE; LED_0603_1608Metric_Pad1.05x0.95mm_HandSolder
D8: PRTR5V0U2X; SOT-143
D9: D_Schottky; DIOM5127X229N
D10: SK6812MINI; LED_SK6812MINI_PLCC4_3.5x3.5mm_P1.75mm
F1, F2, F3, F4, F5, F6: Polyfuse; Fuse_0805_2012Metric_Pad1.15x1.40mm_HandSolder
F7: Fuse; 0031.7701.11
FB1, FB2: FerriteBead; L_0805_2012Metric_Pad1.15x1.40mm_HandSolder
FID1, FID2, FID3: Fiducial; Fiducial_1mm_Mask2mm
H1, H2, H3, H4: MountingHole; MountingHole_3.2mm_M3_DIN965_Pad
J1, J2, J3: Conn_01x16_Pin; TE_1-84952-6_1x16-1MP_P1.0mm_Horizontal
J4: Conn_01x04_Socket; JST_XH_B4B-XH-A_1x04_P2.50mm_Vertical
J5, J6: 1778667; SHDRRA6W70P0X250_1X6_1670X750X510P
J7: Conn_02x05_Odd_Even; PinSocket_2x05_P1.27mm_Vertical
J8: USB_C_Receptacle_USB2.0; USB_C_Receptacle_HRO_TYPE-C-31-M-12
J9: Conn_01x02_Socket; JST_XH_B2B-XH-A_1x02_P2.50mm_Vertical
JP1, JP2: Jumper_2_Open; SolderJumper-2_P1.3mm_Open_RoundedPad1.0x1.5mm
R1, R6, R8: 330; R_0603_1608Metric_Pad0.98x0.95mm_HandSolder
R2: 2.2k; R_0603_1608Metric_Pad0.98x0.95mm_HandSolder
R3, R4, R9, R10, R14, R15: 62; R_0603_1608Metric_Pad0.98x0.95mm_HandSolder
R5, R7: 470; R_0603_1608Metric_Pad0.98x0.95mm_HandSolder
R11, R12, R13, R16, R17, R18: 4.7k; R_0603_1608Metric_Pad0.98x0.95mm_HandSolder
R19, R20, R21: 10k; R_0603_1608Metric_Pad0.98x0.95mm_HandSolder
R22, R23: 27; R_0603_1608Metric_Pad0.98x0.95mm_HandSolder
R24: 1m; R_0603_1608Metric_Pad0.98x0.95mm_HandSolder
R25: 100k; R_0603_1608Metric_Pad0.98x0.95mm_HandSolder
R26, R27: 5.1k 1%; R_0603_1608Metric_Pad0.98x0.95mm_HandSolder
SW1, SW2: SW_Push; SW_SPST_PTS810
TP1: IO_1; TestPoint_Pad_D1.5mm
TP2: IO_2; TestPoint_Pad_D1.5mm
TP3: IO_3; TestPoint_Pad_D1.5mm
TP4: IO_4; TestPoint_Pad_D1.5mm
TP5: IO_5; TestPoint_Pad_D1.5mm
TP6: IO_6; TestPoint_Pad_D1.5mm
TP7: IO_7; TestPoint_Pad_D1.5mm
TP8: CLK_A1; TestPoint_Pad_D1.5mm
TP9: CLK_A0; TestPoint_Pad_D1.5mm
TP10: INT4; TestPoint_Pad_D1.5mm
TP11: INT5; TestPoint_Pad_D1.5mm
TP12: NEOPIXEL; TestPoint_Pad_D1.5mm
TP13: SWD; TestPoint_Pad_D1.5mm
TP14: CLK; TestPoint_Pad_D1.5mm
TP15: SCL_SEN; TestPoint_Pad_D1.5mm
TP16: SDA_SEN; TestPoint_Pad_D1.5mm
TP17: RST; TestPoint_Pad_D1.5mm
TP18: CS; TestPoint_Pad_D1.5mm
TP19: SCK; TestPoint_Pad_D1.5mm
TP20: MOSI; TestPoint_Pad_D1.5mm
TP21: MISO; TestPoint_Pad_D1.5mm
TP22: SCL; TestPoint_Pad_D1.5mm
TP23: SDA; TestPoint_Pad_D1.5mm
TP24: SCL_IO; TestPoint_Pad_D1.5mm
TP25: SDA_IO; TestPoint_Pad_D1.5mm
TP26: 5V; TestPoint_Pad_D1.5mm
TP27: 3.3V; TestPoint_Pad_D1.5mm
TP28: D-; TestPoint_Pad_D1.5mm
TP29: D+; TestPoint_Pad_D1.5mm
TP30: 5V_AUX; TestPoint_Pad_D1.5mm
TP31: ADR_LED1; TestPoint_Pad_D1.5mm
TP32: ADR_LED2; TestPoint_Pad_D1.5mm
TP33: ADR_LED3; TestPoint_Pad_D1.5mm
TP34: ADR_LED4; TestPoint_Pad_D1.5mm
TP35: ADR_LED5; TestPoint_Pad_D1.5mm
TP36: ADR_LED6; TestPoint_Pad_D1.5mm
TP37: OUT_LED1; TestPoint_Pad_D1.5mm
TP38: OUT_LED2; TestPoint_Pad_D1.5mm
TP39: OUT_LED3; TestPoint_Pad_D1.5mm
TP40: OUT_LED4; TestPoint_Pad_D1.5mm
TP41: OUT_LED5; TestPoint_Pad_D1.5mm
TP42: OUT_LED6; TestPoint_Pad_D1.5mm
U1: ATSAMD21G18A-M; QFN-48-1EP_7x7mm_P0.5mm_EP5.15x5.15mm
U2: IS25LP032D-JLLE; SON127P600X500X75-9N-D
U3: AP2112K-3.3; SOT-23-5
U4, U5: SN74AHCT125RGYR; RGY-_S-PVQFN-N14_
Y1: 32.768mHz; Crystal_SMD_3215-2Pin_3.2x1.5mm
kibuzzard-6574D62C: G***; kibuzzard-6574D62C
kibuzzard-6574D547: G***; kibuzzard-6574D547
kibuzzard-6574D579: G***; kibuzzard-6574D579
kibuzzard-6574D710: G***; kibuzzard-6574D710
kibuzzard-6574D849: G***; kibuzzard-6574D849
kibuzzard-6574DAA4: G***; kibuzzard-6574DAA4
kibuzzard-6574DAAD: G***; kibuzzard-6574DAAD
kibuzzard-65744A4B, kibuzzard-65744A4B#2: G***; kibuzzard-65744A4B
kibuzzard-65744A5E, kibuzzard-65744A5E#2: G***; kibuzzard-65744A5E
kibuzzard-65744A66, kibuzzard-65744A66#2: G***; kibuzzard-65744A66
kibuzzard-65744A78, kibuzzard-65744A78#2: G***; kibuzzard-65744A78
kibuzzard-65744A88, kibuzzard-65744A88#2: G***; kibuzzard-65744A88
kibuzzard-65744B8B: G***; kibuzzard-65744B8B
kibuzzard-65744BA2: G***; kibuzzard-65744BA2
kibuzzard-65744BAF: G***; kibuzzard-65744BAF
kibuzzard-65744BC6: G***; kibuzzard-65744BC6
kibuzzard-65744BCE: G***; kibuzzard-65744BCE
kibuzzard-65744F4B: G***; kibuzzard-65744F4B
kibuzzard-65744F40: G***; kibuzzard-65744F40
kibuzzard-65744FA3: G***; kibuzzard-65744FA3
kibuzzard-65744FAF: G***; kibuzzard-65744FAF
kibuzzard-657449AF: G***; kibuzzard-657449AF
kibuzzard-6574499F: G***; kibuzzard-6574499F
kibuzzard-6574640D: G***; kibuzzard-6574640D

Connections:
+3V3: C3.2, C4.2, C12.1, C13.1, C14.1, C15.1, C18.1, D10.4 (VDD), F2.2, F4.2, F6.2, FB2.1, J4.1, J5.3, J6.3, J7.1, JP2.2 (B), R5.1, R11.1, R12.2, R13.1, R16.2, R17.1, R18.2, R19.1, R20.2, R21.2, TP27.1, U1.17 (VDDIO), U1.36 (VDDIO), U1.44 (VDDIN), U2.3 (~WP(IO2)), U2.7 (~HOLD(IO3)), U2.8 (VCC)
+5V: C19.1, C20.1, D9.1 (K), F1.2, F3.2, F5.2, J5.1, J6.1, JP1.2 (B), R2.1, TP26.1, U4.14 (VCC), U5.14 (VCC)
/ADR_LED1: TP31.1, U1.28 (PA19), U4.5 (2A)
/ADR_LED2: TP32.1, U1.27 (PA18), U4.2 (1A)
/ADR_LED3: TP33.1, U1.30 (PA21), U4.9 (3A)
/ADR_LED4: TP34.1, U1.29 (PA20), U4.12 (4A)
/ADR_LED5: TP35.1, U1.7 (PB08), U5.8 (3Y)
/ADR_LED6: TP36.1, U1.8 (PB09), U5.11 (4Y)
/AREF: C11.1, U1.4 (PA03)
/D2_FLASHMISO: TP21.1, U1.23 (PA14), U2.2 (SO(IO1))
/D3_FLASHSCK: TP19.1, U1.14 (PA09), U2.6 (SCK)
/D4_FLASHMOSI: TP20.1, U1.13 (PA08), U2.5 (SI(IO0))
/D5_HEALTH: R1.1, U1.24 (PA15)
/D8_NEOPIXEL: D10.3 (DIN), TP12.1, U1.11 (PA06)
/D14_HB: R6.1, U1.3 (PA02)
/INT4: J5.6, TP10.1, U1.9 (PA04)
/INT5: J6.6, TP11.1, U1.10 (PA05)
/IO_1: J1.8, TP1.1, U1.15 (PA10)
/IO_2: J1.9, TP2.1, U1.16 (PA11)
/IO_3: R21.1, SW2.1, TP3.1, U1.47 (PB02)
/IO_4: J2.8, TP4.1, U1.19 (PB10)
/IO_5: J2.9, TP5.1, U1.20 (PB11)
/IO_6: J3.8, TP6.1, U1.37 (PB22)
/IO_7: J3.9, TP7.1, U1.38 (PB23)
/OUT_LED1: R4.1, TP37.1, U4.6 (2Y)
/OUT_LED2: R3.1, TP38.1, U4.3 (1Y)
/OUT_LED3: R9.1, TP39.1, U4.8 (3Y)
/OUT_LED4: R10.1, TP40.1, U4.11 (4Y)
/OUT_LED5: R14.1, TP41.1, U5.9 (3A)
/OUT_LED6: R15.1, TP42.1, U5.12 (4A)
/PA0_XTAL: C1.2, TP9.1, U1.1 (PA00), Y1.2
/PA1_XTAL: C2.2, TP8.1, U1.2 (PA01), Y1.1
/PA7_FLASH_CS: R19.2, TP18.1, U1.12 (PA07), U2.1 (~CE)
/Power/3.3v: C7.1, C9.1, JP2.1 (A), U3.5 (VOUT)
/Power/SHIELD: C6.1, J8.S1 (SHIELD), R24.1
/RXLED: R8.1, U1.48 (PB03)
/SCL: J5.4, J6.4, R13.2, TP22.1, U1.32 (PA23)
/SCL_IO: J1.12, J2.12, J3.12, R17.2, TP24.1, U1.22 (PA13)
/SCL_SENSOR_D13: J4.3, R11.2, TP15.1, U1.26 (PA17)
/SDA: J5.5, J6.5, R16.1, TP23.1, U1.31 (PA22)
/SDA_IO: J1.11, J2.11, J3.11, R18.1, TP25.1, U1.21 (PA12)
/SDA_SENSOR_D11: J4.4, R12.1, TP16.1, U1.25 (PA16)
/SWCLK: J7.4, TP14.1, U1.45 (PA30)
/SWDIO: J7.2, TP13.1, U1.46 (PA31)
/TXLED: R7.1, U1.39 (PA27)
/USB_D+: D8.3 (I/O2), J8.A6 (D+), J8.B6 (D+), R23.1, TP29.1
/USB_D-: D8.2 (I/O1), J8.A7 (D-), J8.B7 (D-), R22.1, TP28.1
/USB_TERM_D+: R23.2, U1.34 (PA25)
/USB_TERM_D-: R22.2, U1.33 (PA24)
/VDDANA: C16.1, C17.1, FB2.2, U1.6 (VDDANA)
/VDDCORE: C10.2, U1.43 (VDDCORE)
/~RESET: J7.10, R20.1, SW1.1, TP17.1, U1.40 (~RESET)
GNDD: C1.1, C2.1, C3.1, C4.1, C5.2, C6.2, C7.2, C8.2, C9.2, C10.1, C11.2, C12.2, C13.2, C14.2, C15.2, C16.2, C17.2, C18.2, C19.2, C20.2, D1.1 (K), D2.1 (K), D3.1 (K), D4.1 (K), D5.1 (K), D6.1 (K), D8.1 (GND), D10.2 (VSS), J1.3, J1.6, J1.7, J1.10, J1.13, J1.16, J2.3, J2.6, J2.7, J2.10, J2.13, J2.16, J3.3, J3.6, J3.7, J3.10, J3.13, J3.16, J4.2, J5.2, J6.2, J7.3, J7.5, J8.A1 (GND), J8.A12 (GND), J8.B1 (GND), J8.B12 (GND), J9.1, R24.2, R26.2, R27.2, SW1.2, SW2.2, U1.5 (GNDANA), U1.18 (GND), U1.35 (GND), U1.42 (GND), U1.49 (EP), U2.4 (GND), U2.9 (EP), U3.2 (GND), U4.1 (1~OE), U4.4 (2~OE), U4.7 (GND), U4.10 (3~OE), U4.13 (4~OE), U4.15 (THERMAL_PAD), U5.1 (1~OE), U5.4 (2~OE), U5.7 (GND), U5.10 (3~OE), U5.13 (4~OE), U5.15 (THERMAL_PAD)
unnamed: D1.2 (A), R1.2
unnamed: D2.2 (A), R2.2
unnamed: D3.2 (A), R5.2
unnamed: D4.2 (A), R6.2
unnamed: D5.2 (A), R7.2
unnamed: D6.2 (A), R8.2
unnamed: D9.2 (A), F7.1
unnamed: FB1.1, J8.A4 (VBUS), J8.A9 (VBUS), J8.B4 (VBUS), J8.B9 (VBUS)
unnamed: F1.1, J1.1, J1.2
unnamed: F2.1, J1.4, J1.5
unnamed: J1.14, R3.2
unnamed: J1.15, R4.2
unnamed: F3.1, J2.1, J2.2
unnamed: F4.1, J2.4, J2.5
unnamed: J2.14, R9.2
unnamed: J2.15, R10.2
unnamed: F5.1, J3.1, J3.2
unnamed: F6.1, J3.4, J3.5
unnamed: J3.14, R14.2
unnamed: J3.15, R15.2
unnamed: J8.A5 (CC1), R27.1
unnamed: J8.B5 (CC2), R26.1
unnamed: F7.2, J9.2, TP30.1
unnamed: R25.2, U3.3 (EN)
VBUS: C5.1, C8.1, D8.4 (VCC), FB1.2, JP1.1 (A), R25.1, U3.1 (VIN)
